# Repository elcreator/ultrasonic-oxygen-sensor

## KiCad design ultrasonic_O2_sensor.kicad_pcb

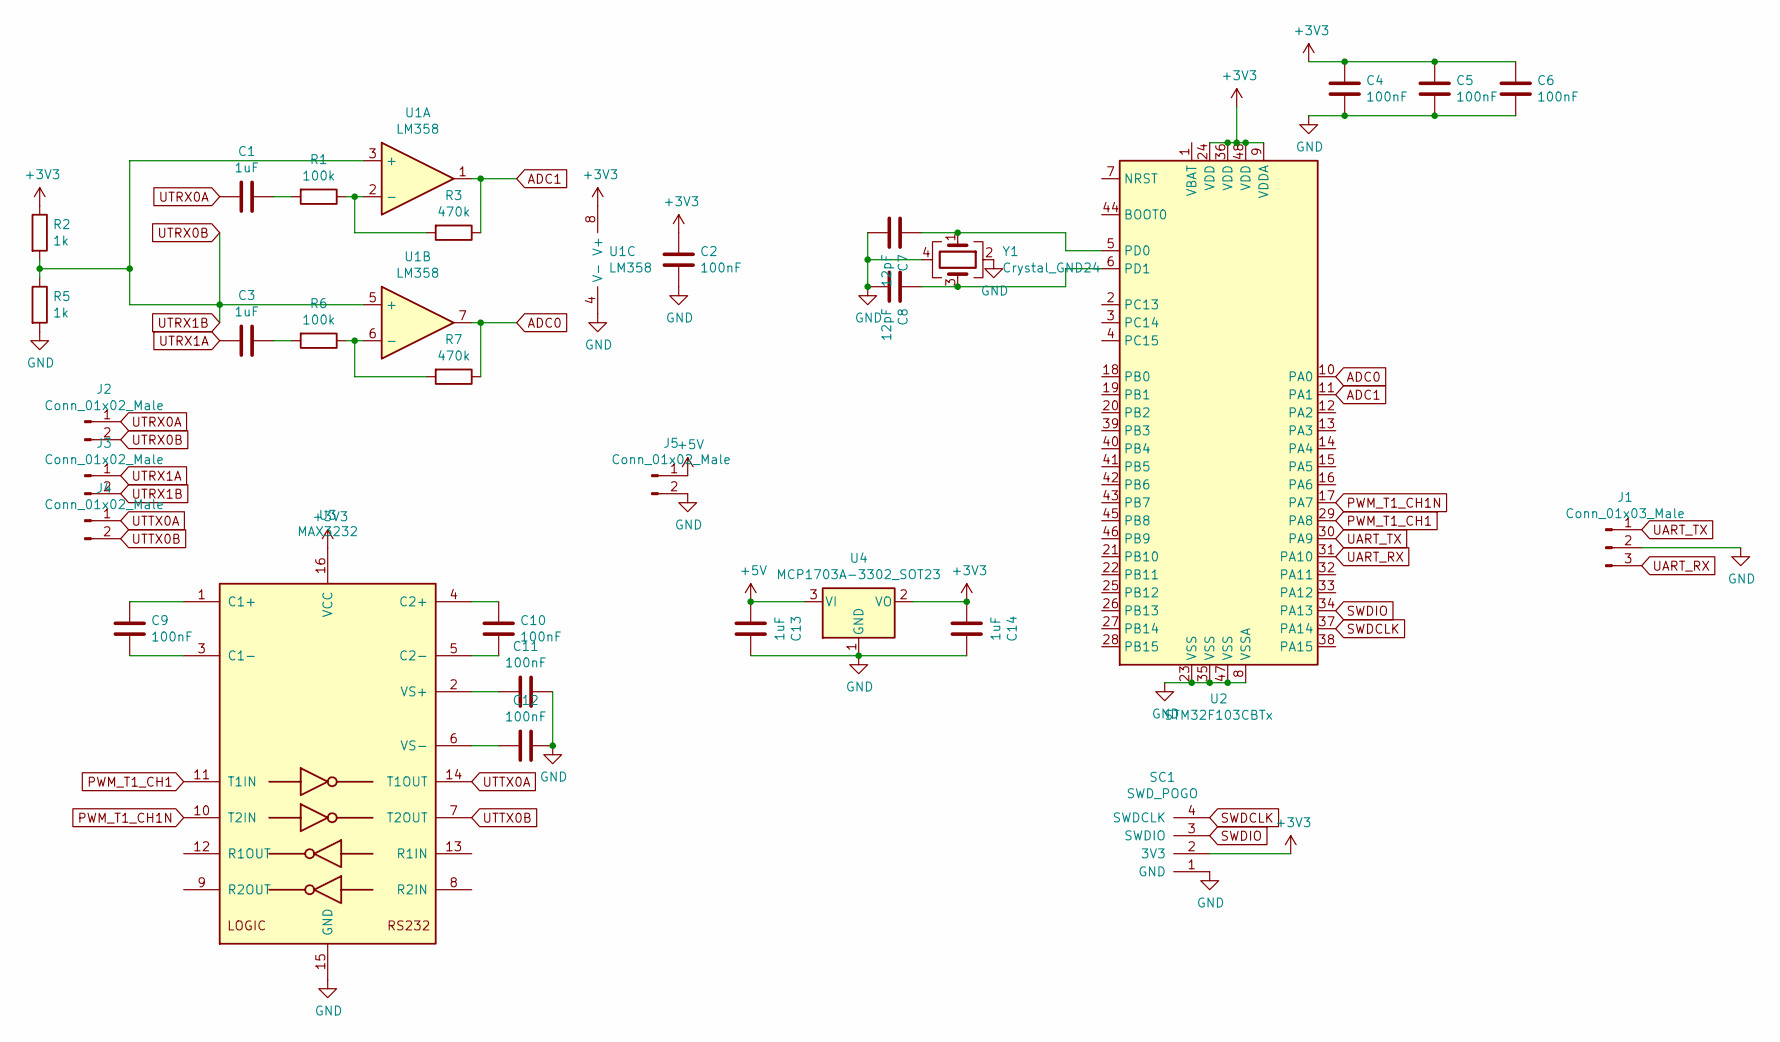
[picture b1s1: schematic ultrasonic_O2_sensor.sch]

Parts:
C1, C3, C13, C14: 1uF; C_0805_2012Metric
C2, C4, C5, C6, C9, C10, C11, C12: 100nF; C_0805_2012Metric
C7, C8: 12pF; C_0805_2012Metric
J1: Conn_01x03_Male; PinHeader_1x03_P2.54mm_Vertical_SMD_Pin1Left
J2, J3, J4, J5: Conn_01x02_Male; PinHeader_2x01_P2.54mm_Vertical_SMD
R1, R6: 100k; R_0805_2012Metric
R2, R5: 1k; R_0805_2012Metric
R3, R7: 470k; R_0805_2012Metric
SC1: SWD_POGO
U1: LM358; SOIC-8_3.9x4.9mm_P1.27mm
U2: STM32F103CBTx; LQFP-48_7x7mm_P0.5mm
U3: MAX3232; SOIC-16W_7.5x10.3mm_P1.27mm
U4: MCP1703A-3302_SOT23; SOT-23
Y1: Crystal_GND24; Crystal_SMD_3225-4Pin_3.2x2.5mm_HandSoldering

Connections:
+3V3: C2.2, C4.2, C5.2, C6.2, C14.2, R2.1, SC1.2 (3V3), U1.8 (V+), U2.9 (VDDA), U2.24 (VDD), U2.36 (VDD), U2.48 (VDD), U3.16 (VCC), U4.2 (VO)
+5V: C13.2, J5.1, U4.3 (VI)
ADC0: R7.1, U1.7, U2.10 (PA0)
ADC1: R3.1, U1.1, U2.11 (PA1)
GND: C2.1, C4.1, C5.1, C6.1, C7.1, C8.1, C11.2, C12.2, C13.1, C14.1, J1.2, J5.2, R5.2, SC1.1 (GND), U1.4 (V-), U2.8 (VSSA), U2.23 (VSS), U2.35 (VSS), U2.47 (VSS), U3.15 (GND), U4.1 (GND), Y1.2, Y1.4
unnamed: C1.1, R1.2
unnamed: C3.1, R6.2
unnamed: C7.2, U2.5 (PD0), Y1.1
unnamed: C8.2, U2.6 (PD1), Y1.3
unnamed: C9.1, U3.3 (C1-)
unnamed: C9.2, U3.1 (C1+)
unnamed: C10.1, U3.5 (C2-)
unnamed: C10.2, U3.4 (C2+)
unnamed: C11.1, U3.2 (VS+)
unnamed: C12.1, U3.6 (VS-)
unnamed: R1.1, R3.2, U1.2 (-)
unnamed: R6.1, R7.2, U1.6 (-)
PWM_T1_CH1: U2.29 (PA8), U3.11 (T1IN)
PWM_T1_CH1N: U2.17 (PA7), U3.10 (T2IN)
SWDCLK: SC1.4 (SWDCLK), U2.37 (PA14)
SWDIO: SC1.3 (SWDIO), U2.34 (PA13)
UART_RX: J1.3, U2.31 (PA10)
UART_TX: J1.1, U2.30 (PA9)
UTRX0A: C1.2, J2.1
UTRX0B: J2.2, J3.2, R2.2, R5.1, U1.3 (+), U1.5 (+)
UTRX1A: C3.2, J3.1
UTTX0A: J4.1, U3.14 (T1OUT)
UTTX0B: J4.2, U3.7 (T2OUT)

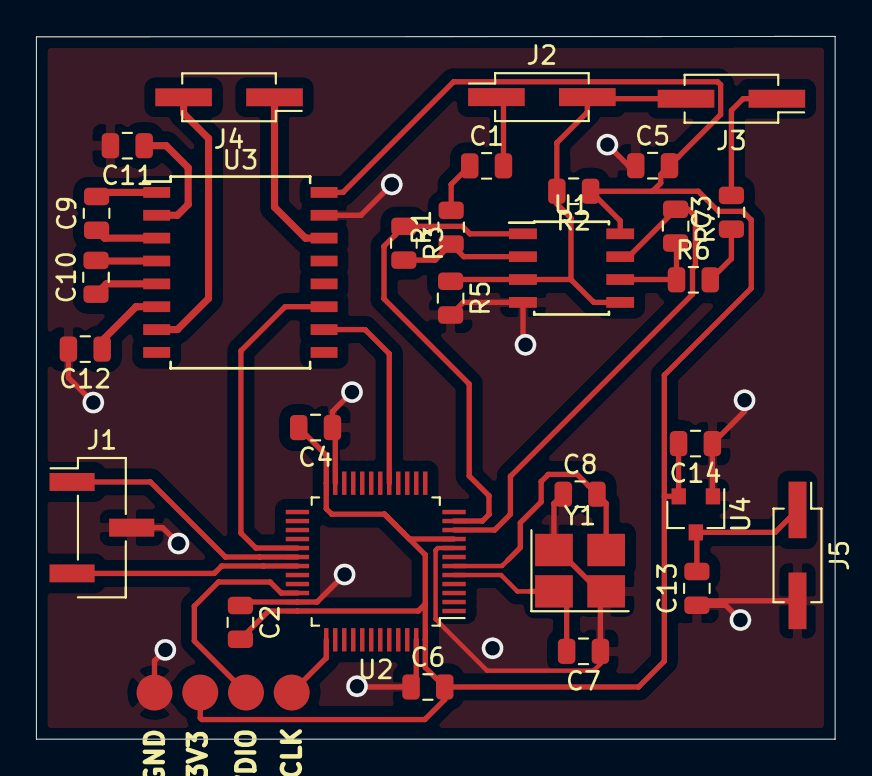
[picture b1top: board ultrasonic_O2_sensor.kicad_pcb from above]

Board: 2 copper layers, 44.4 x 39.0 mm, 31 parts (0 on the bottom side), 28 nets.

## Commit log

2020-04-15 first version of the PCB
